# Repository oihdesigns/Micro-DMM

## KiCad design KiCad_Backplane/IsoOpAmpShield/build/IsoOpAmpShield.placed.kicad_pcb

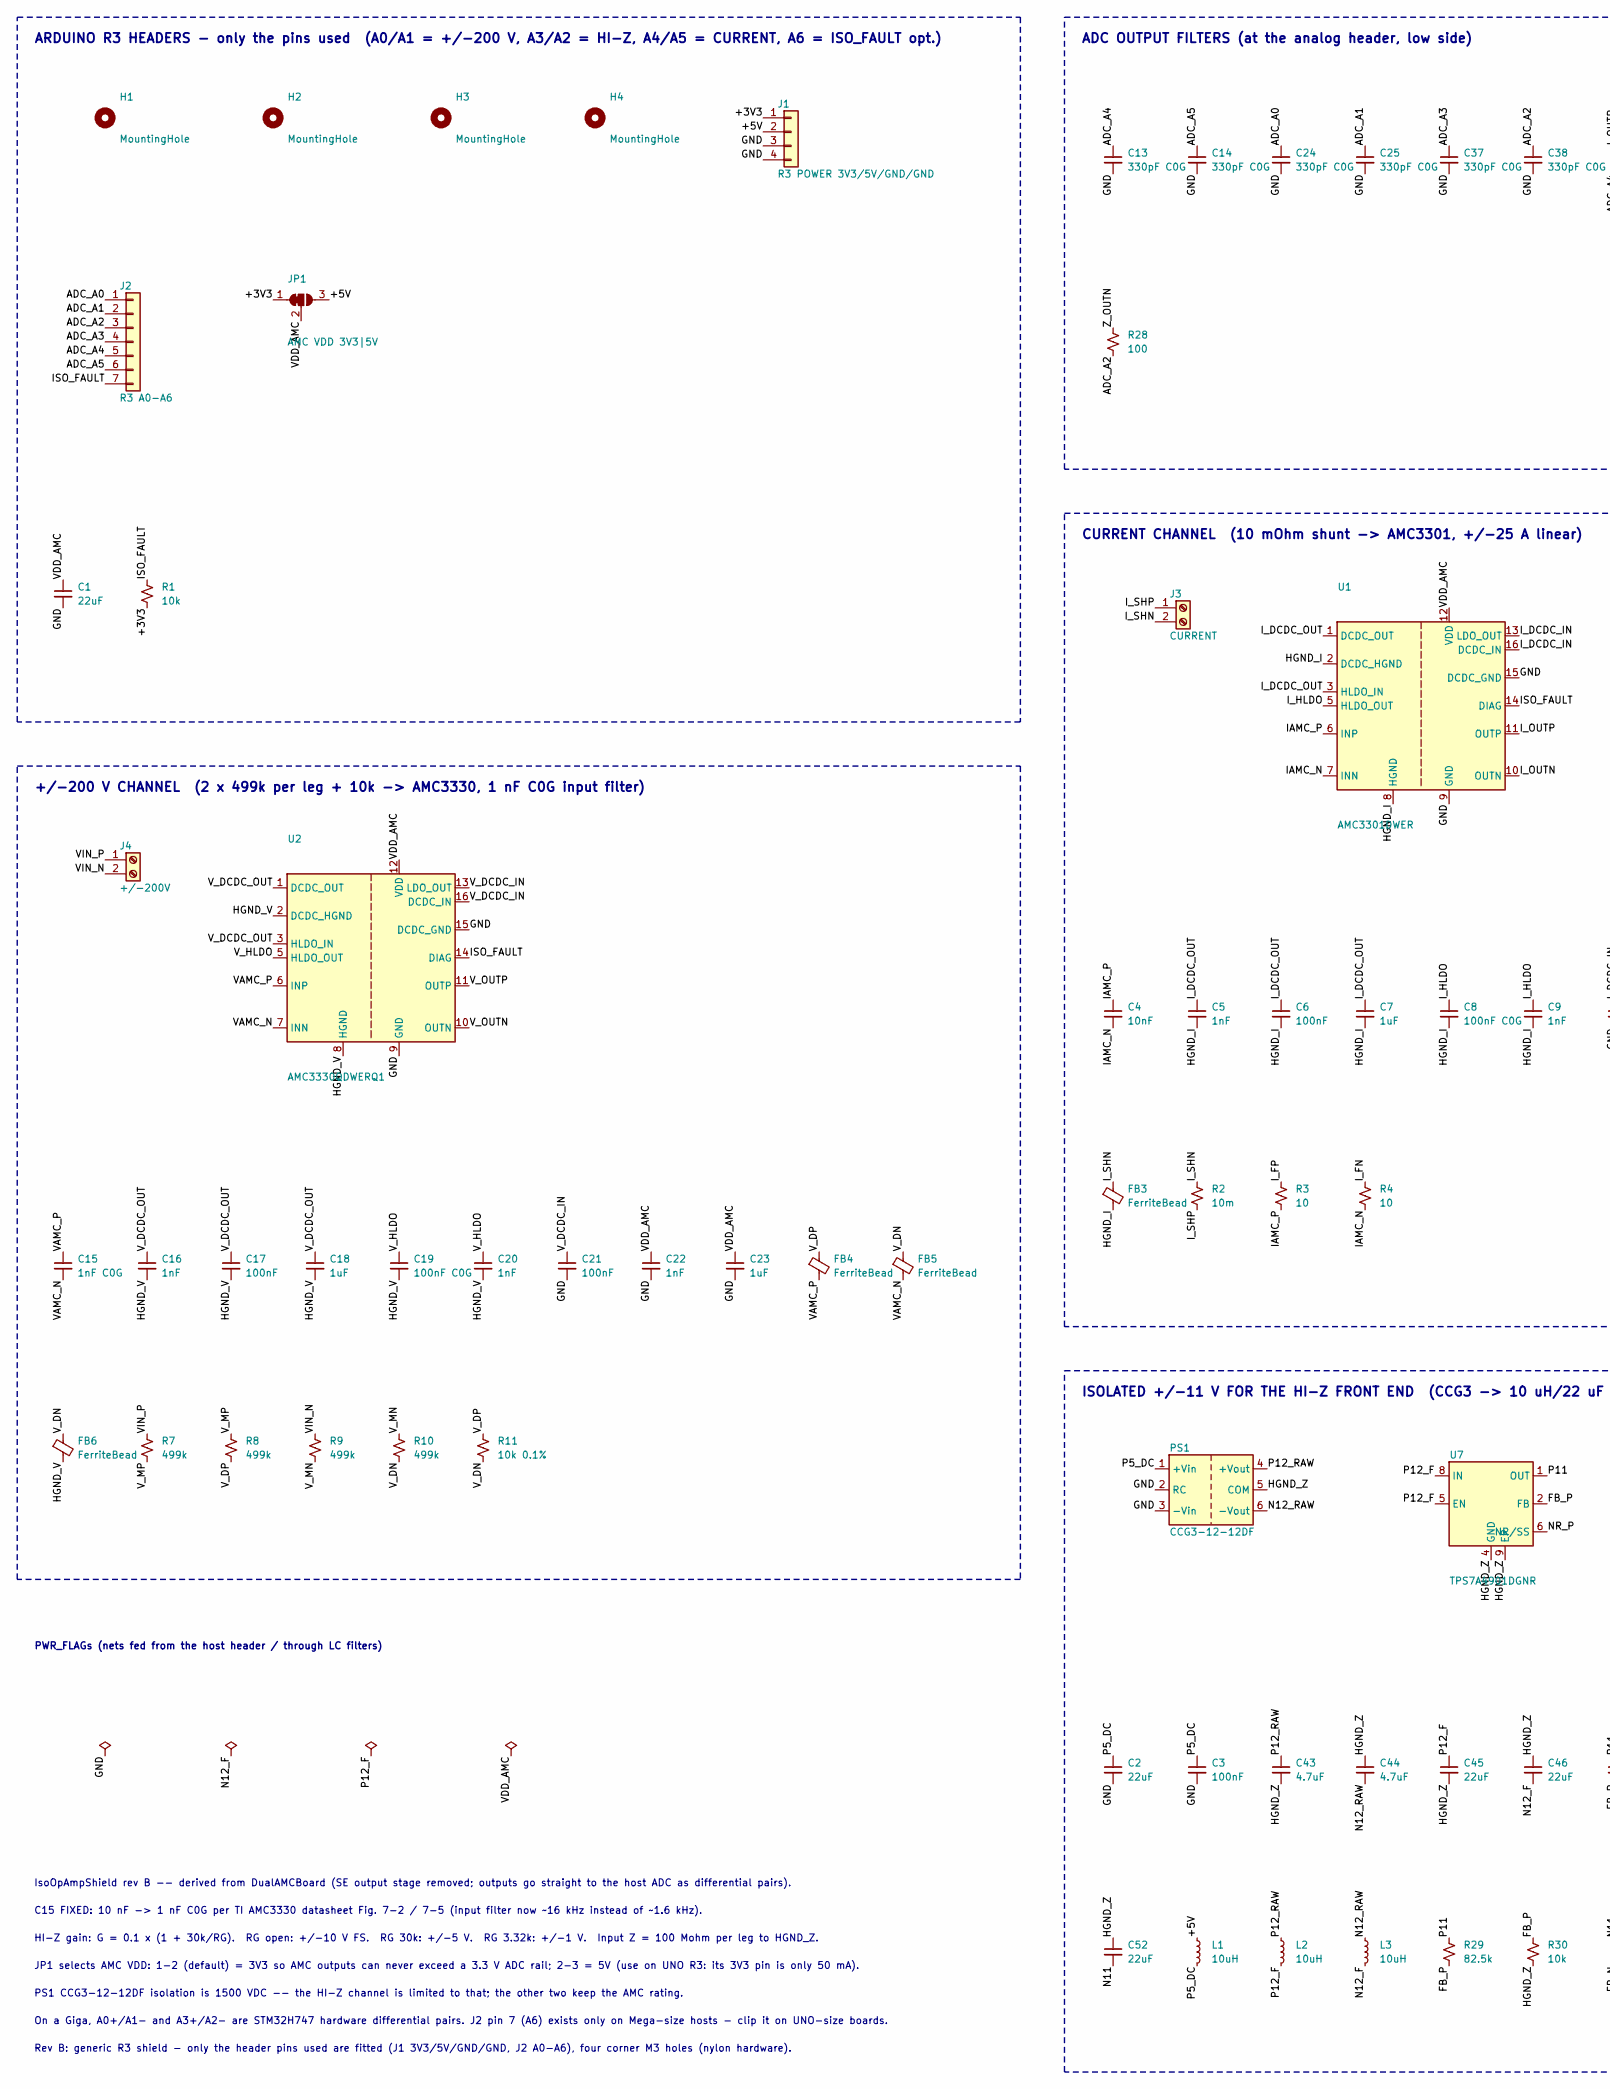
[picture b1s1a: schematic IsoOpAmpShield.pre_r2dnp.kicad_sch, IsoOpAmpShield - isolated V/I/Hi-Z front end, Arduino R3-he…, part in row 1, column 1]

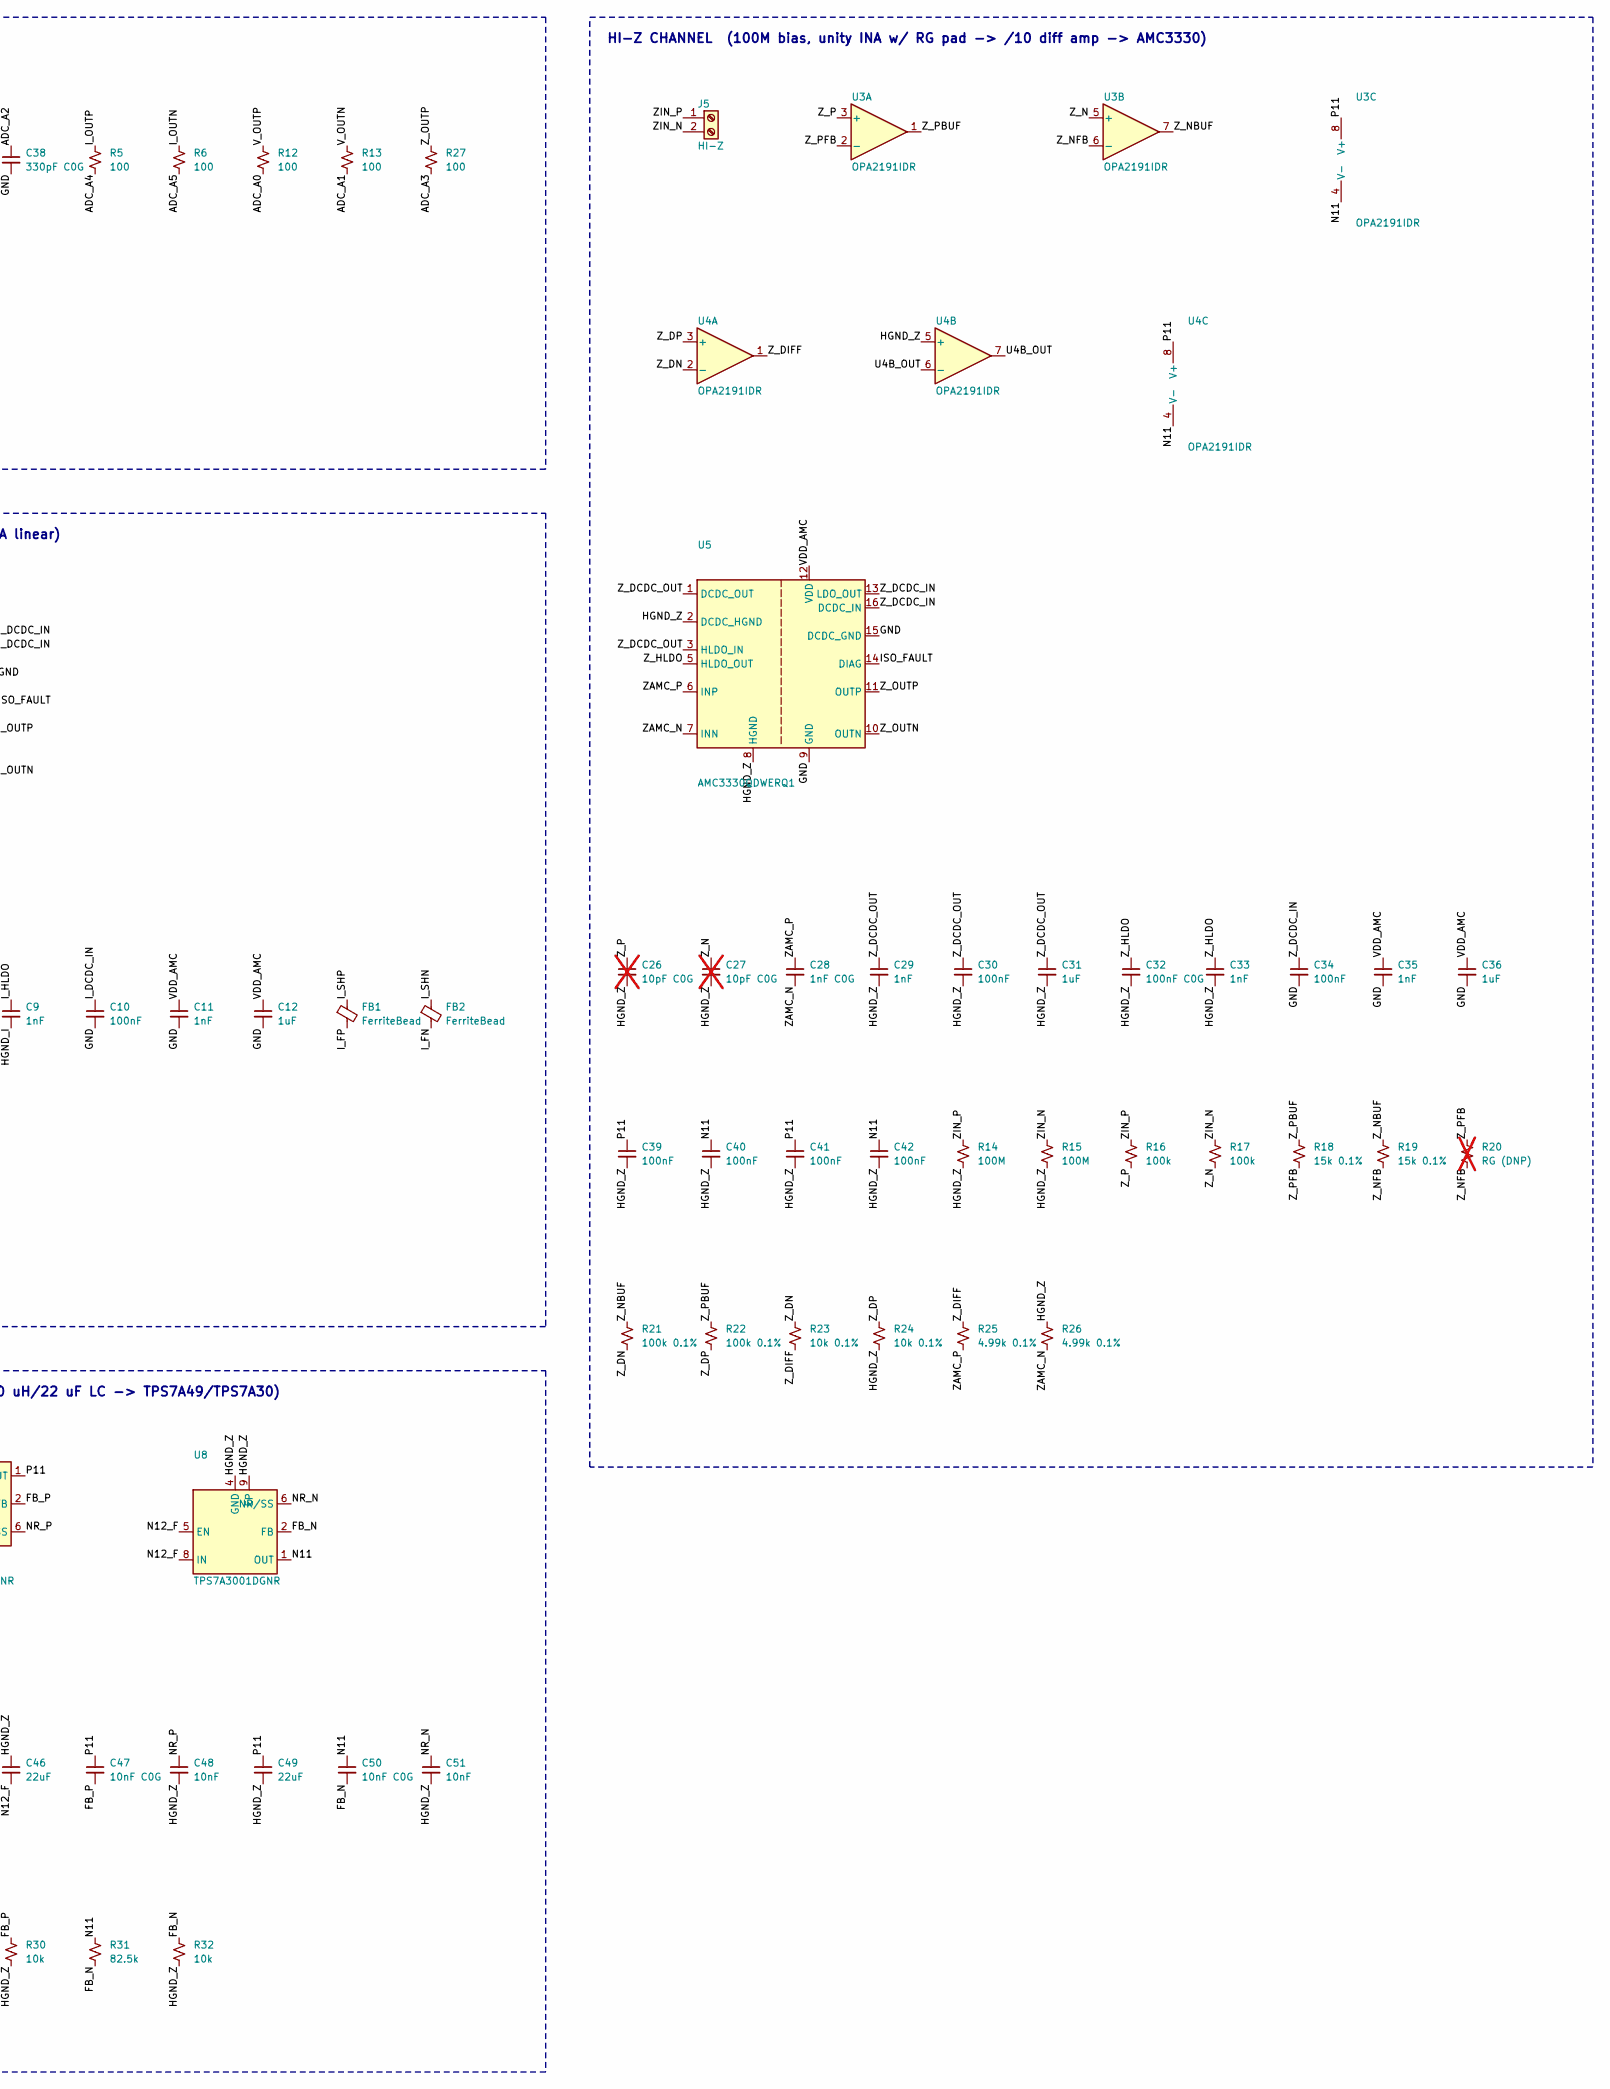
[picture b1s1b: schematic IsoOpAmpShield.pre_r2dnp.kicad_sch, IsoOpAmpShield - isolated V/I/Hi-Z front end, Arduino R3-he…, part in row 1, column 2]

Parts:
C1, C2, C45, C46, C49, C52: 22uF; C_0805_2012Metric_Pad1.18x1.45mm_HandSolder
C3, C6, C10, C17, C21, C30, C34, C39, C40, C41, C42: 100nF; C_0603_1608Metric_Pad1.08x0.95mm_HandSolder
C4: 10nF; C_0805_2012Metric_Pad1.18x1.45mm_HandSolder
C5, C16, C29: 1nF; C_0603_1608Metric_Pad1.08x0.95mm_HandSolder
C7, C18, C31: 1uF; C_0603_1608Metric_Pad1.08x0.95mm_HandSolder
C8, C19, C32: 100nF C0G; C_1206_3216Metric_Pad1.33x1.80mm_HandSolder
C9, C11, C20, C22, C33, C35: 1nF; C_1206_3216Metric_Pad1.33x1.80mm_HandSolder
C12, C23, C36: 1uF; C_1206_3216Metric_Pad1.33x1.80mm_HandSolder
C13, C14, C24, C25, C37, C38: 330pF C0G; C_0603_1608Metric_Pad1.08x0.95mm_HandSolder
C15, C28: 1nF C0G; C_0805_2012Metric_Pad1.18x1.45mm_HandSolder
C26, C27: 10pF C0G; C_0603_1608Metric_Pad1.08x0.95mm_HandSolder; not fitted
C43, C44: 4.7uF; C_0805_2012Metric_Pad1.18x1.45mm_HandSolder
C47, C50: 10nF C0G; C_0603_1608Metric_Pad1.08x0.95mm_HandSolder
C48, C51: 10nF; C_0603_1608Metric_Pad1.08x0.95mm_HandSolder
FB1, FB2, FB3, FB4, FB5, FB6: FerriteBead; L_0402_1005Metric_Pad0.77x0.64mm_HandSolder
H1, H2, H3, H4: MountingHole; MountingHole_3.2mm_M3_NPTH
J1: R3 POWER 3V3/5V/GND/GND; PinHeader_1x04_P2.54mm_Vertical
J2: R3 A0-A6; PinHeader_1x07_P2.54mm_Vertical
J3: CURRENT; TerminalBlock_RND_205-00232_1x02_P5.08mm_Horizontal
J4: +/-200V; TerminalBlock_RND_205-00232_1x02_P5.08mm_Horizontal
J5: HI-Z; TerminalBlock_RND_205-00232_1x02_P5.08mm_Horizontal
JP1: AMC VDD 3V3|5V; SolderJumper-3_P1.3mm_Bridged12_RoundedPad1.0x1.5mm
L1, L2, L3: 10uH; L_1210_3225Metric_Pad1.42x2.65mm_HandSolder
PS1: CCG3-12-12DF; TDK_CCG3_Dual_THT
R1, R30, R32: 10k; R_0805_2012Metric_Pad1.20x1.40mm_HandSolder
R2: 10m; R_2010_5025Metric_Pad1.40x2.65mm_HandSolder
R3, R4: 10; R_0805_2012Metric_Pad1.20x1.40mm_HandSolder
R5, R6, R12, R13, R27, R28: 100; R_0805_2012Metric_Pad1.20x1.40mm_HandSolder
R7, R8, R9, R10: 499k; R_0805_2012Metric_Pad1.20x1.40mm_HandSolder
R11, R23, R24: 10k 0.1%; R_0805_2012Metric_Pad1.20x1.40mm_HandSolder
R14, R15: 100M; R_1206_3216Metric_Pad1.30x1.75mm_HandSolder
R16, R17: 100k; R_1206_3216Metric_Pad1.30x1.75mm_HandSolder
R18, R19: 15k 0.1%; R_0805_2012Metric_Pad1.20x1.40mm_HandSolder
R20: RG (DNP); R_0805_2012Metric_Pad1.20x1.40mm_HandSolder; not fitted
R21, R22: 100k 0.1%; R_0805_2012Metric_Pad1.20x1.40mm_HandSolder
R25, R26: 4.99k 0.1%; R_0805_2012Metric_Pad1.20x1.40mm_HandSolder
R29, R31: 82.5k; R_0805_2012Metric_Pad1.20x1.40mm_HandSolder
U1: AMC3301DWER; SOIC-16W_7.5x10.3mm_P1.27mm
U2, U5: AMC3330QDWERQ1; SOIC-16W_7.5x10.3mm_P1.27mm
U3, U4: OPA2191IDR; SOIC-8_3.9x4.9mm_P1.27mm
U7: TPS7A4901DGNR; HVSSOP-8-1EP_3x3mm_P0.65mm_EP1.57x1.89mm
U8: TPS7A3001DGNR; HVSSOP-8-1EP_3x3mm_P0.65mm_EP1.57x1.89mm

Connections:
/+5V: J1.2, J1.5, JP1.3 (B), L1.1
/ADC_A0: C24.1, J2.1, R12.2
/ADC_A1: C25.1, J2.2, R13.2
/ADC_A2: C38.1, J2.3, R28.2
/ADC_A3: C37.1, J2.4, R27.2
/ADC_A4: C13.1, J2.5, R5.2
/ADC_A5: C14.1, J2.6, R6.2
/FB_N: C50.2, R31.2, R32.1, U8.2 (FB)
/FB_P: C47.2, R29.2, R30.1, U7.2 (FB)
/HGND_I: C5.2, C6.2, C7.2, C8.2, C9.2, FB3.2, U1.2 (DCDC_HGND), U1.8 (HGND)
/HGND_V: C16.2, C17.2, C18.2, C19.2, C20.2, FB6.2, U2.2 (DCDC_HGND), U2.8 (HGND)
/HGND_Z: C26.2, C27.2, C29.2, C30.2, C31.2, C32.2, C33.2, C39.2, C40.2, C41.2, C42.2, C43.2, C44.1, C45.2, C46.1, C48.2, C49.2, C51.2, C52.1, PS1.5 (COM), R14.2, R15.2, R24.2, R26.1, R30.2, R32.2, U4.5 (+), U5.2 (DCDC_HGND), U5.8 (HGND), U7.4 (GND), U7.9 (EP), U8.4 (GND), U8.9 (EP)
/IAMC_N: C4.2, R4.2, U1.7 (INN)
/IAMC_P: C4.1, R3.2, U1.6 (INP)
/ISO_FAULT: J2.7, R1.1, U1.14 (DIAG), U2.14 (DIAG), U5.14 (DIAG)
/I_DCDC_IN: C10.1, U1.13 (LDO_OUT), U1.16 (DCDC_IN)
/I_DCDC_OUT: C5.1, C6.1, C7.1, U1.1 (DCDC_OUT), U1.3 (HLDO_IN)
/I_FN: FB2.2, R4.1
/I_FP: FB1.2, R3.1
/I_HLDO: C8.1, C9.1, U1.5 (HLDO_OUT)
/I_OUTN: R6.1, U1.10 (OUTN)
/I_OUTP: R5.1, U1.11 (OUTP)
/I_SHN: FB2.1, FB3.1, J3.2, R2.1
/I_SHP: FB1.1, J3.1, R2.2
/N11: C40.1, C42.1, C50.1, C52.2, R31.1, U3.4 (V-), U4.4 (V-), U8.1 (OUT)
/N12_F: C46.2, L3.2, U8.5 (EN), U8.8 (IN)
/N12_RAW: C44.2, L3.1, PS1.6 (-Vout)
/NR_N: C51.1, U8.6 (NR/SS)
/NR_P: C48.1, U7.6 (NR/SS)
/P5_DC: C2.1, C3.1, L1.2, PS1.1 (+Vin)
/P11: C39.1, C41.1, C47.1, C49.1, R29.1, U3.8 (V+), U4.8 (V+), U7.1 (OUT)
/P12_F: C45.1, L2.2, U7.5 (EN), U7.8 (IN)
/P12_RAW: C43.1, L2.1, PS1.4 (+Vout)
/U4B_OUT: U4.6 (-), U4.7
/VAMC_N: C15.2, FB5.2, U2.7 (INN)
/VAMC_P: C15.1, FB4.2, U2.6 (INP)
/VDD_AMC: C1.1, C11.1, C12.1, C22.1, C23.1, C35.1, C36.1, JP1.2 (C), U1.12 (VDD), U2.12 (VDD), U5.12 (VDD)
/VIN_N: J4.2, R9.1
/VIN_P: J4.1, R7.1
/V_DCDC_IN: C21.1, U2.13 (LDO_OUT), U2.16 (DCDC_IN)
/V_DCDC_OUT: C16.1, C17.1, C18.1, U2.1 (DCDC_OUT), U2.3 (HLDO_IN)
/V_DN: FB5.1, FB6.1, R10.2, R11.2
/V_DP: FB4.1, R8.2, R11.1
/V_HLDO: C19.1, C20.1, U2.5 (HLDO_OUT)
/V_MN: R9.2, R10.1
/V_MP: R7.2, R8.1
/V_OUTN: R13.1, U2.10 (OUTN)
/V_OUTP: R12.1, U2.11 (OUTP)
/ZAMC_N: C28.2, R26.2, U5.7 (INN)
/ZAMC_P: C28.1, R25.2, U5.6 (INP)
/ZIN_N: J5.2, R15.1, R17.1
/ZIN_P: J5.1, R14.1, R16.1
/Z_DCDC_IN: C34.1, U5.13 (LDO_OUT), U5.16 (DCDC_IN)
/Z_DCDC_OUT: C29.1, C30.1, C31.1, U5.1 (DCDC_OUT), U5.3 (HLDO_IN)
/Z_DIFF: R23.2, R25.1, U4.1
/Z_DN: R21.2, R23.1, U4.2 (-)
/Z_DP: R22.2, R24.1, U4.3 (+)
/Z_HLDO: C32.1, C33.1, U5.5 (HLDO_OUT)
/Z_N: C27.1, R17.2, U3.5 (+)
/Z_NBUF: R19.1, R21.1, U3.7
/Z_NFB: R19.2, R20.2, U3.6 (-)
/Z_OUTN: R28.1, U5.10 (OUTN)
/Z_OUTP: R27.1, U5.11 (OUTP)
/Z_P: C26.1, R16.2, U3.3 (+)
/Z_PBUF: R18.1, R22.1, U3.1
/Z_PFB: R18.2, R20.1, U3.2 (-)

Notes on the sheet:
ARDUINO R3 HEADERS - only the pins used (A0/A1 = +/-200 V, A3/A2 = HI-Z, A4/A5 = CURRENT, A6 = ISO_FAULT opt.)
+/-200 V CHANNEL (2 x 499k per leg + 10k -> AMC3330, 1 nF C0G input filter)
ADC OUTPUT FILTERS (at the analog header, low side)
CURRENT CHANNEL (10 mOhm shunt -> AMC3301, +/-25 A linear)
ISOLATED +/-11 V FOR THE HI-Z FRONT END (CCG3 -> 10 uH/22 uF LC -> TPS7A49/TPS7A30)
HI-Z CHANNEL (100M bias, unity INA w/ RG pad -> /10 diff amp -> AMC3330)
PWR_FLAGs (nets fed from the host header / through LC filters)
IsoOpAmpShield rev B -- derived from DualAMCBoard (SE output stage removed; outputs go straight to the host ADC as differential pairs).
C15 FIXED: 10 nF -> 1 nF C0G per TI AMC3330 datasheet Fig. 7-2 / 7-5 (input filter now ~16 kHz instead of ~1.6 kHz).
HI-Z gain: G = 0.1 x (1 + 30k/RG). RG open: +/-10 V FS. RG 30k: +/-5 V. RG 3.32k: +/-1 V. Input Z = 100 Mohm per leg to HGND_Z.
JP1 selects AMC VDD: 1-2 (default) = 3V3 so AMC outputs can never exceed a 3.3 V ADC rail; 2-3 = 5V (use on UNO R3: its 3V3 pin is only 50 mA).
PS1 CCG3-12-12DF isolation is 1500 VDC -- the HI-Z channel is limited to that; the other two keep the AMC rating.
On a Giga, A0+/A1- and A3+/A2- are STM32H747 hardware differential pairs. J2 pin 7 (A6) exists only on Mega-size hosts - clip it on UNO-size boards.
Rev B: generic R3 shield - only the header pins used are fitted (J1 3V3/5V/GND/GND, J2 A0-A6), four corner M3 holes (nylon hardware).

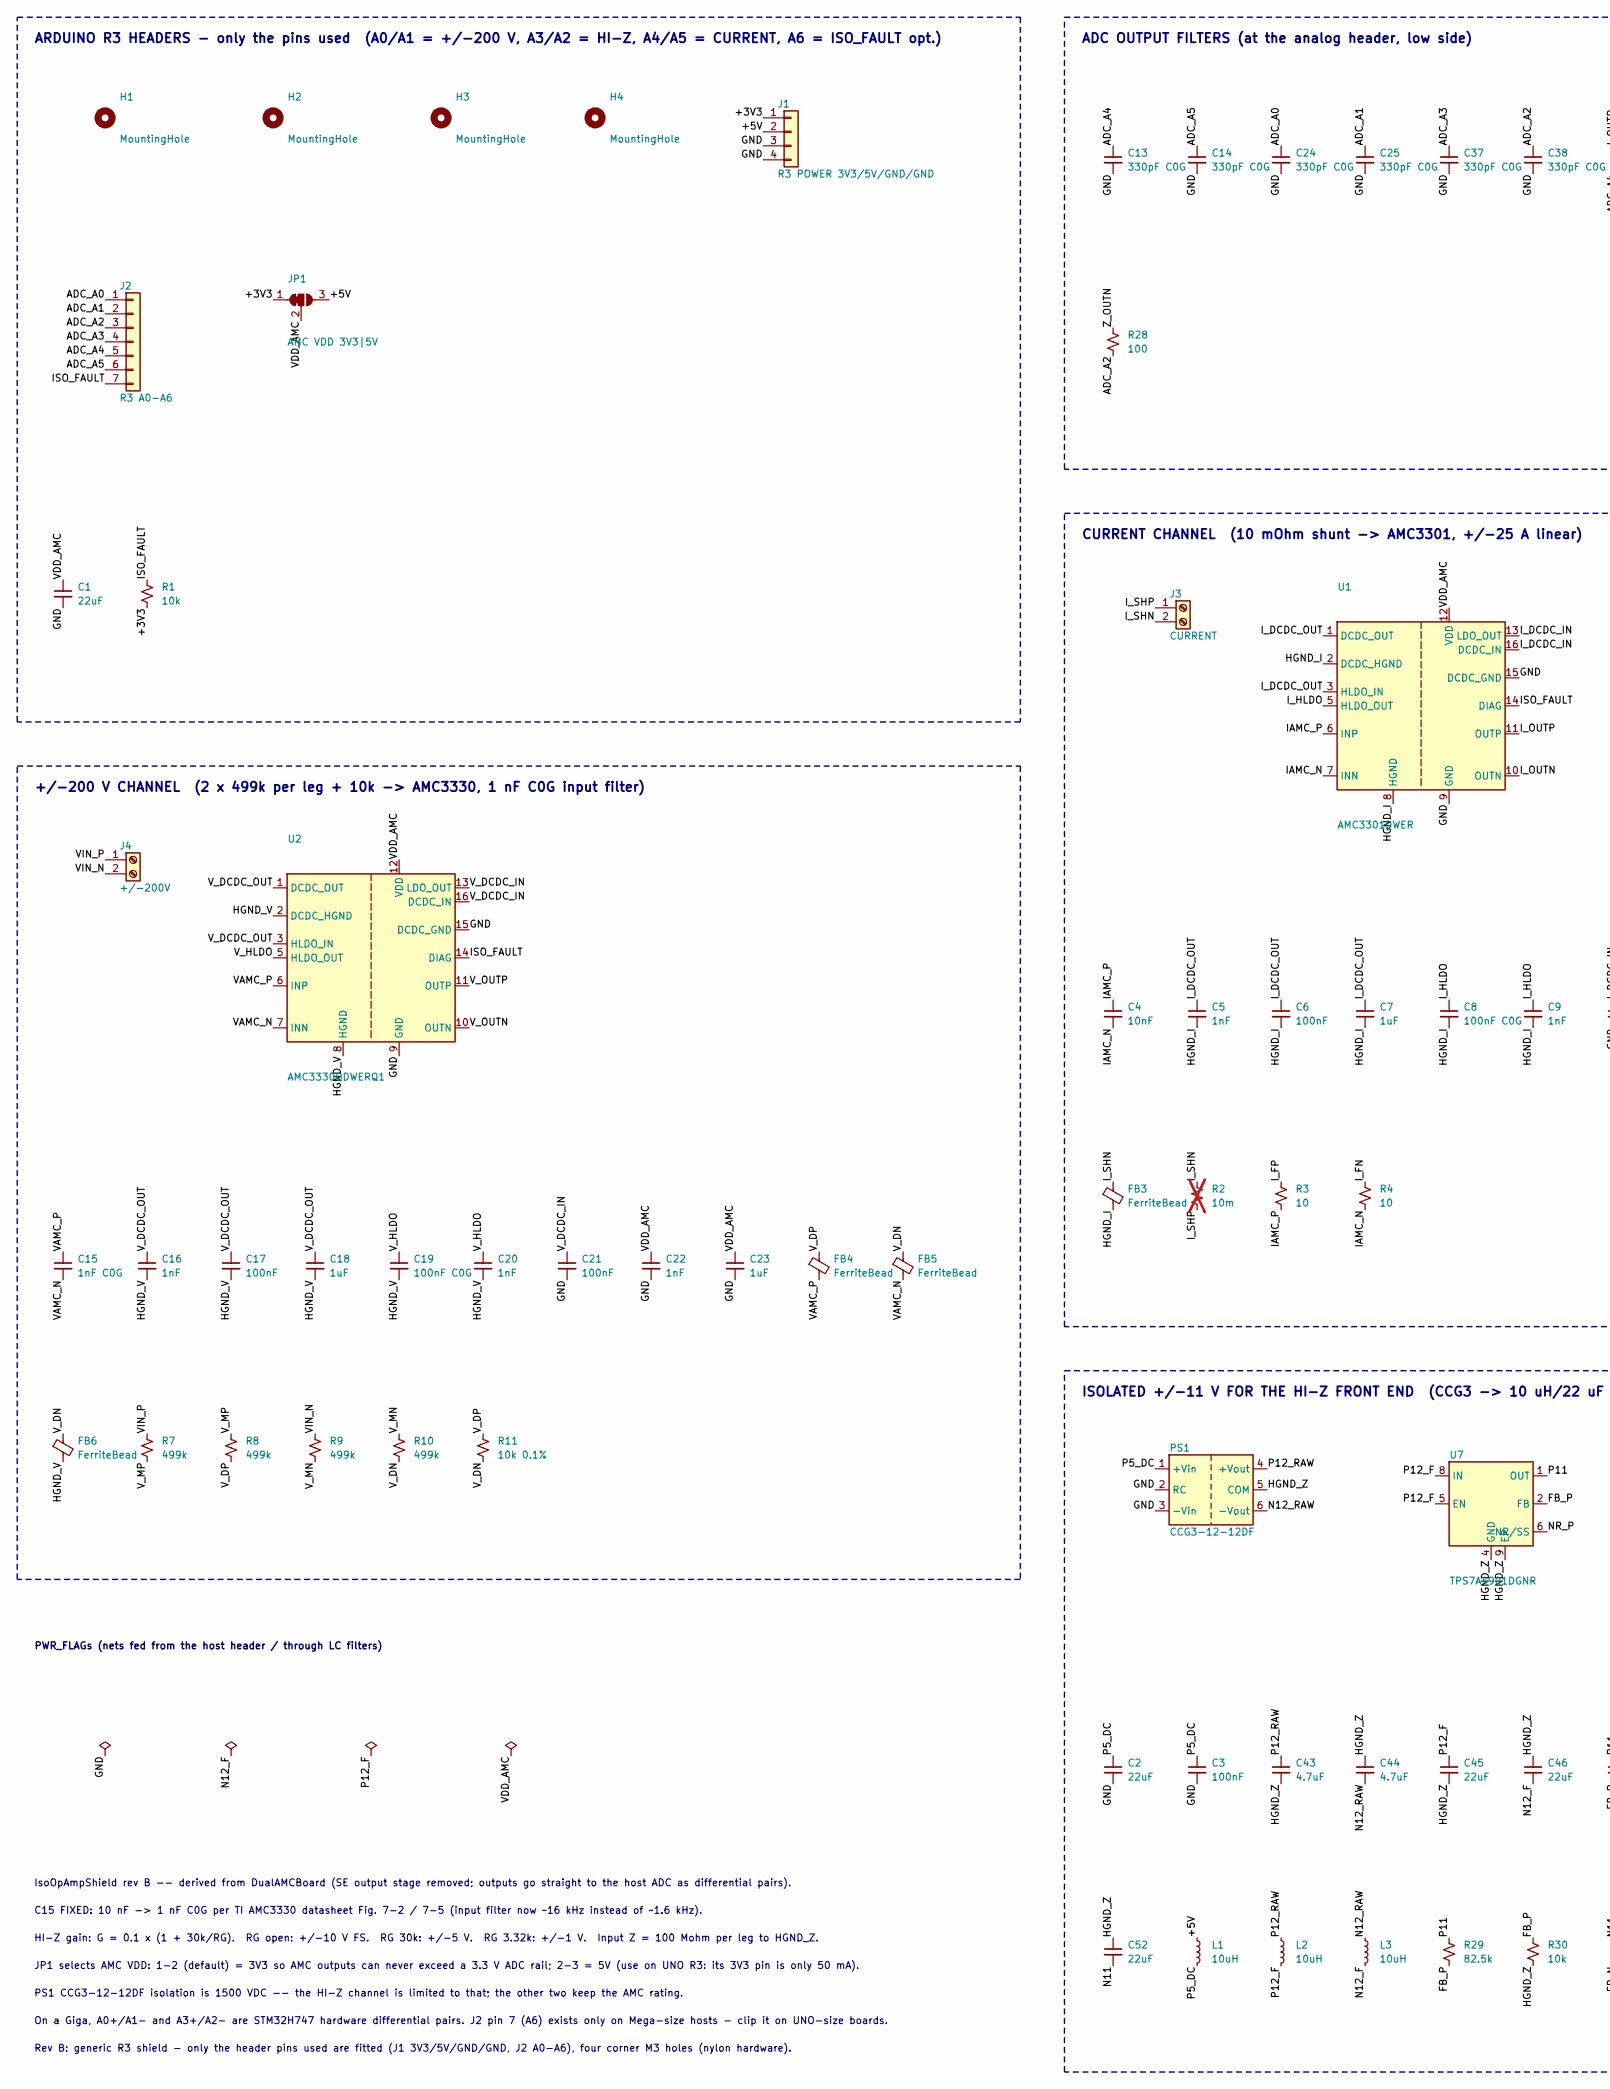
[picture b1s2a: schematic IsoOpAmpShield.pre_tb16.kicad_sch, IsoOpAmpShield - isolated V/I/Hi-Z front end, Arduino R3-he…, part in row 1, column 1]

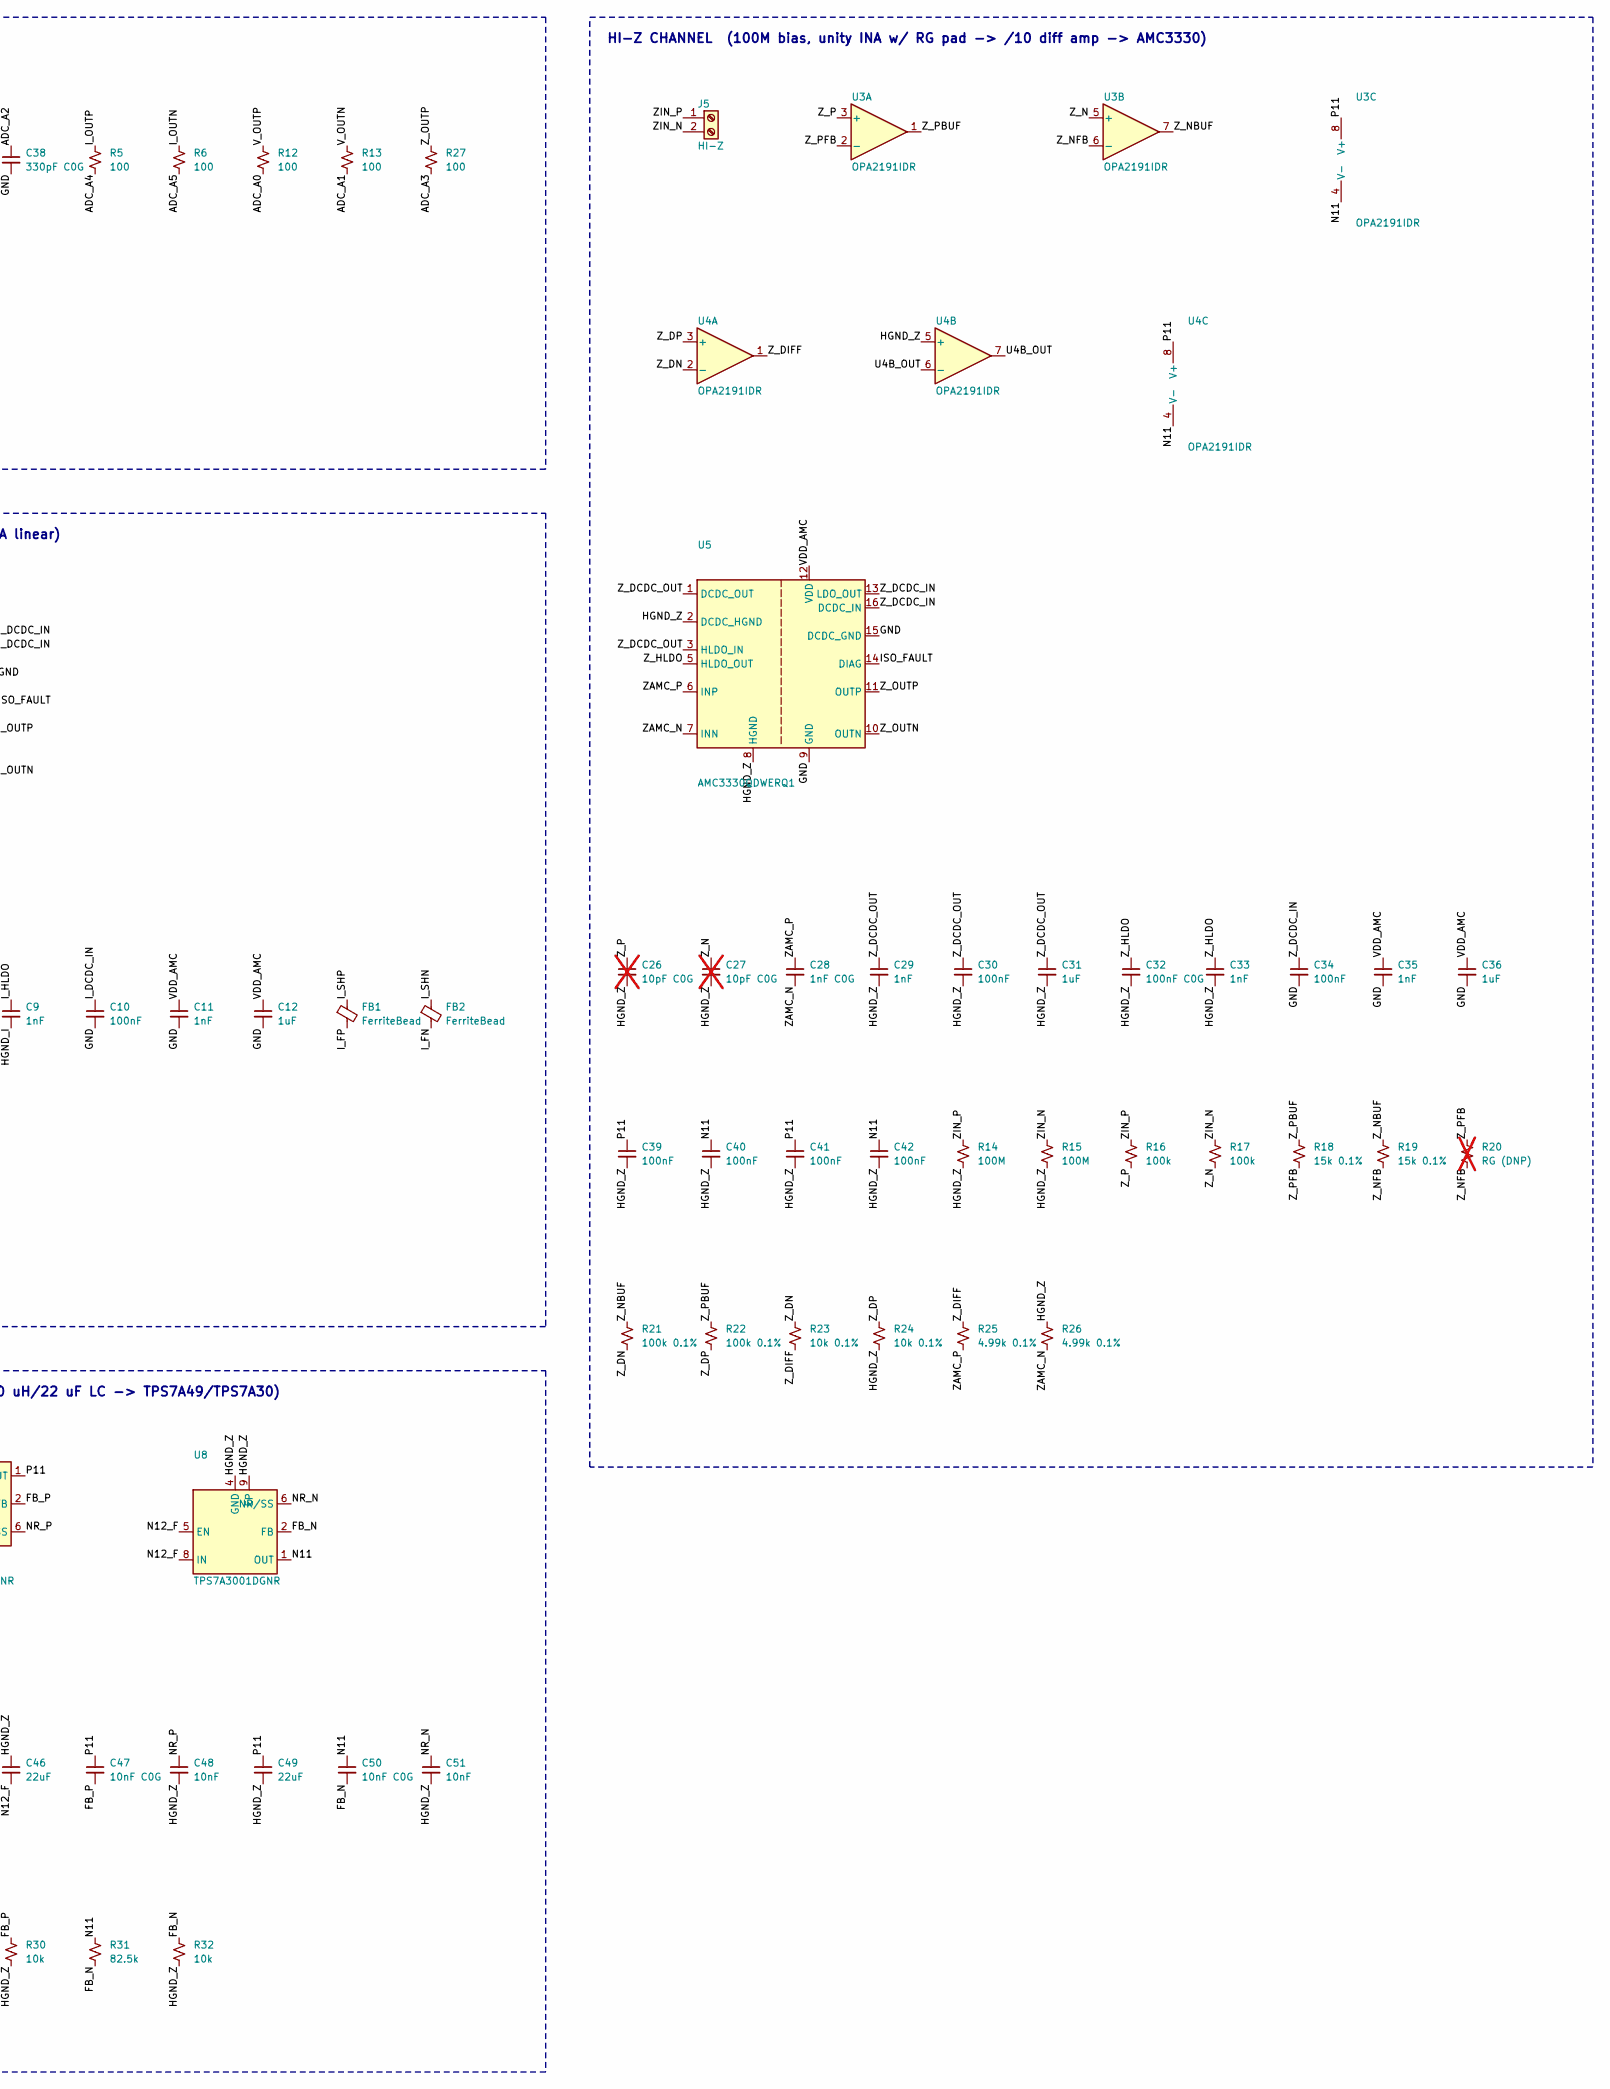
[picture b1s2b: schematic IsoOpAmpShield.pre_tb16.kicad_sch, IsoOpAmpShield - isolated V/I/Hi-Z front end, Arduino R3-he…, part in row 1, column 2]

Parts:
C1, C2, C45, C46, C49, C52: 22uF; C_0805_2012Metric_Pad1.18x1.45mm_HandSolder
C3, C6, C10, C17, C21, C30, C34, C39, C40, C41, C42: 100nF; C_0603_1608Metric_Pad1.08x0.95mm_HandSolder
C4: 10nF; C_0805_2012Metric_Pad1.18x1.45mm_HandSolder
C5, C16, C29: 1nF; C_0603_1608Metric_Pad1.08x0.95mm_HandSolder
C7, C18, C31: 1uF; C_0603_1608Metric_Pad1.08x0.95mm_HandSolder
C8, C19, C32: 100nF C0G; C_1206_3216Metric_Pad1.33x1.80mm_HandSolder
C9, C11, C20, C22, C33, C35: 1nF; C_1206_3216Metric_Pad1.33x1.80mm_HandSolder
C12, C23, C36: 1uF; C_1206_3216Metric_Pad1.33x1.80mm_HandSolder
C13, C14, C24, C25, C37, C38: 330pF C0G; C_0603_1608Metric_Pad1.08x0.95mm_HandSolder
C15, C28: 1nF C0G; C_0805_2012Metric_Pad1.18x1.45mm_HandSolder
C26, C27: 10pF C0G; C_0603_1608Metric_Pad1.08x0.95mm_HandSolder; not fitted
C43, C44: 4.7uF; C_0805_2012Metric_Pad1.18x1.45mm_HandSolder
C47, C50: 10nF C0G; C_0603_1608Metric_Pad1.08x0.95mm_HandSolder
C48, C51: 10nF; C_0603_1608Metric_Pad1.08x0.95mm_HandSolder
FB1, FB2, FB3, FB4, FB5, FB6: FerriteBead; L_0402_1005Metric_Pad0.77x0.64mm_HandSolder
H1, H2, H3, H4: MountingHole; MountingHole_3.2mm_M3_NPTH
J1: R3 POWER 3V3/5V/GND/GND; PinHeader_1x04_P2.54mm_Vertical
J2: R3 A0-A6; PinHeader_1x07_P2.54mm_Vertical
J3: CURRENT; TerminalBlock_RND_205-00232_1x02_P5.08mm_Horizontal
J4: +/-200V; TerminalBlock_RND_205-00232_1x02_P5.08mm_Horizontal
J5: HI-Z; TerminalBlock_RND_205-00232_1x02_P5.08mm_Horizontal
JP1: AMC VDD 3V3|5V; SolderJumper-3_P1.3mm_Bridged12_RoundedPad1.0x1.5mm
L1, L2, L3: 10uH; L_1210_3225Metric_Pad1.42x2.65mm_HandSolder
PS1: CCG3-12-12DF; TDK_CCG3_Dual_THT
R1, R30, R32: 10k; R_0805_2012Metric_Pad1.20x1.40mm_HandSolder
R2: 10m; R_2010_5025Metric_Pad1.40x2.65mm_HandSolder; not fitted
R3, R4: 10; R_0805_2012Metric_Pad1.20x1.40mm_HandSolder
R5, R6, R12, R13, R27, R28: 100; R_0805_2012Metric_Pad1.20x1.40mm_HandSolder
R7, R8, R9, R10: 499k; R_0805_2012Metric_Pad1.20x1.40mm_HandSolder
R11, R23, R24: 10k 0.1%; R_0805_2012Metric_Pad1.20x1.40mm_HandSolder
R14, R15: 100M; R_1206_3216Metric_Pad1.30x1.75mm_HandSolder
R16, R17: 100k; R_1206_3216Metric_Pad1.30x1.75mm_HandSolder
R18, R19: 15k 0.1%; R_0805_2012Metric_Pad1.20x1.40mm_HandSolder
R20: RG (DNP); R_0805_2012Metric_Pad1.20x1.40mm_HandSolder; not fitted
R21, R22: 100k 0.1%; R_0805_2012Metric_Pad1.20x1.40mm_HandSolder
R25, R26: 4.99k 0.1%; R_0805_2012Metric_Pad1.20x1.40mm_HandSolder
R29, R31: 82.5k; R_0805_2012Metric_Pad1.20x1.40mm_HandSolder
U1: AMC3301DWER; SOIC-16W_7.5x10.3mm_P1.27mm
U2, U5: AMC3330QDWERQ1; SOIC-16W_7.5x10.3mm_P1.27mm
U3, U4: OPA2191IDR; SOIC-8_3.9x4.9mm_P1.27mm
U7: TPS7A4901DGNR; HVSSOP-8-1EP_3x3mm_P0.65mm_EP1.57x1.89mm
U8: TPS7A3001DGNR; HVSSOP-8-1EP_3x3mm_P0.65mm_EP1.57x1.89mm

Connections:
/+5V: J1.2, J1.5, JP1.3 (B), L1.1
/ADC_A0: C24.1, J2.1, R12.2
/ADC_A1: C25.1, J2.2, R13.2
/ADC_A2: C38.1, J2.3, R28.2
/ADC_A3: C37.1, J2.4, R27.2
/ADC_A4: C13.1, J2.5, R5.2
/ADC_A5: C14.1, J2.6, R6.2
/FB_N: C50.2, R31.2, R32.1, U8.2 (FB)
/FB_P: C47.2, R29.2, R30.1, U7.2 (FB)
/HGND_I: C5.2, C6.2, C7.2, C8.2, C9.2, FB3.2, U1.2 (DCDC_HGND), U1.8 (HGND)
/HGND_V: C16.2, C17.2, C18.2, C19.2, C20.2, FB6.2, U2.2 (DCDC_HGND), U2.8 (HGND)
/HGND_Z: C26.2, C27.2, C29.2, C30.2, C31.2, C32.2, C33.2, C39.2, C40.2, C41.2, C42.2, C43.2, C44.1, C45.2, C46.1, C48.2, C49.2, C51.2, C52.1, PS1.5 (COM), R14.2, R15.2, R24.2, R26.1, R30.2, R32.2, U4.5 (+), U5.2 (DCDC_HGND), U5.8 (HGND), U7.4 (GND), U7.9 (EP), U8.4 (GND), U8.9 (EP)
/IAMC_N: C4.2, R4.2, U1.7 (INN)
/IAMC_P: C4.1, R3.2, U1.6 (INP)
/ISO_FAULT: J2.7, R1.1, U1.14 (DIAG), U2.14 (DIAG), U5.14 (DIAG)
/I_DCDC_IN: C10.1, U1.13 (LDO_OUT), U1.16 (DCDC_IN)
/I_DCDC_OUT: C5.1, C6.1, C7.1, U1.1 (DCDC_OUT), U1.3 (HLDO_IN)
/I_FN: FB2.2, R4.1
/I_FP: FB1.2, R3.1
/I_HLDO: C8.1, C9.1, U1.5 (HLDO_OUT)
/I_OUTN: R6.1, U1.10 (OUTN)
/I_OUTP: R5.1, U1.11 (OUTP)
/I_SHN: FB2.1, FB3.1, J3.2, R2.1
/I_SHP: FB1.1, J3.1, R2.2
/N11: C40.1, C42.1, C50.1, C52.2, R31.1, U3.4 (V-), U4.4 (V-), U8.1 (OUT)
/N12_F: C46.2, L3.2, U8.5 (EN), U8.8 (IN)
/N12_RAW: C44.2, L3.1, PS1.6 (-Vout)
/NR_N: C51.1, U8.6 (NR/SS)
/NR_P: C48.1, U7.6 (NR/SS)
/P5_DC: C2.1, C3.1, L1.2, PS1.1 (+Vin)
/P11: C39.1, C41.1, C47.1, C49.1, R29.1, U3.8 (V+), U4.8 (V+), U7.1 (OUT)
/P12_F: C45.1, L2.2, U7.5 (EN), U7.8 (IN)
/P12_RAW: C43.1, L2.1, PS1.4 (+Vout)
/U4B_OUT: U4.6 (-), U4.7
/VAMC_N: C15.2, FB5.2, U2.7 (INN)
/VAMC_P: C15.1, FB4.2, U2.6 (INP)
/VDD_AMC: C1.1, C11.1, C12.1, C22.1, C23.1, C35.1, C36.1, JP1.2 (C), U1.12 (VDD), U2.12 (VDD), U5.12 (VDD)
/VIN_N: J4.2, R9.1
/VIN_P: J4.1, R7.1
/V_DCDC_IN: C21.1, U2.13 (LDO_OUT), U2.16 (DCDC_IN)
/V_DCDC_OUT: C16.1, C17.1, C18.1, U2.1 (DCDC_OUT), U2.3 (HLDO_IN)
/V_DN: FB5.1, FB6.1, R10.2, R11.2
/V_DP: FB4.1, R8.2, R11.1
/V_HLDO: C19.1, C20.1, U2.5 (HLDO_OUT)
/V_MN: R9.2, R10.1
/V_MP: R7.2, R8.1
/V_OUTN: R13.1, U2.10 (OUTN)
/V_OUTP: R12.1, U2.11 (OUTP)
/ZAMC_N: C28.2, R26.2, U5.7 (INN)
/ZAMC_P: C28.1, R25.2, U5.6 (INP)
/ZIN_N: J5.2, R15.1, R17.1
/ZIN_P: J5.1, R14.1, R16.1
/Z_DCDC_IN: C34.1, U5.13 (LDO_OUT), U5.16 (DCDC_IN)
/Z_DCDC_OUT: C29.1, C30.1, C31.1, U5.1 (DCDC_OUT), U5.3 (HLDO_IN)
/Z_DIFF: R23.2, R25.1, U4.1
/Z_DN: R21.2, R23.1, U4.2 (-)
/Z_DP: R22.2, R24.1, U4.3 (+)
/Z_HLDO: C32.1, C33.1, U5.5 (HLDO_OUT)
/Z_N: C27.1, R17.2, U3.5 (+)
/Z_NBUF: R19.1, R21.1, U3.7
/Z_NFB: R19.2, R20.2, U3.6 (-)
/Z_OUTN: R28.1, U5.10 (OUTN)
/Z_OUTP: R27.1, U5.11 (OUTP)
/Z_P: C26.1, R16.2, U3.3 (+)
/Z_PBUF: R18.1, R22.1, U3.1
/Z_PFB: R18.2, R20.1, U3.2 (-)

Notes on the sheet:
ARDUINO R3 HEADERS - only the pins used (A0/A1 = +/-200 V, A3/A2 = HI-Z, A4/A5 = CURRENT, A6 = ISO_FAULT opt.)
+/-200 V CHANNEL (2 x 499k per leg + 10k -> AMC3330, 1 nF C0G input filter)
ADC OUTPUT FILTERS (at the analog header, low side)
CURRENT CHANNEL (10 mOhm shunt -> AMC3301, +/-25 A linear)
ISOLATED +/-11 V FOR THE HI-Z FRONT END (CCG3 -> 10 uH/22 uF LC -> TPS7A49/TPS7A30)
HI-Z CHANNEL (100M bias, unity INA w/ RG pad -> /10 diff amp -> AMC3330)
PWR_FLAGs (nets fed from the host header / through LC filters)
IsoOpAmpShield rev B -- derived from DualAMCBoard (SE output stage removed; outputs go straight to the host ADC as differential pairs).
C15 FIXED: 10 nF -> 1 nF C0G per TI AMC3330 datasheet Fig. 7-2 / 7-5 (input filter now ~16 kHz instead of ~1.6 kHz).
HI-Z gain: G = 0.1 x (1 + 30k/RG). RG open: +/-10 V FS. RG 30k: +/-5 V. RG 3.32k: +/-1 V. Input Z = 100 Mohm per leg to HGND_Z.
JP1 selects AMC VDD: 1-2 (default) = 3V3 so AMC outputs can never exceed a 3.3 V ADC rail; 2-3 = 5V (use on UNO R3: its 3V3 pin is only 50 mA).
PS1 CCG3-12-12DF isolation is 1500 VDC -- the HI-Z channel is limited to that; the other two keep the AMC rating.
On a Giga, A0+/A1- and A3+/A2- are STM32H747 hardware differential pairs. J2 pin 7 (A6) exists only on Mega-size hosts - clip it on UNO-size boards.
Rev B: generic R3 shield - only the header pins used are fitted (J1 3V3/5V/GND/GND, J2 A0-A6), four corner M3 holes (nylon hardware).

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
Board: 4 copper layers, 110 parts (0 on the bottom side), 68 nets, no tracks yet.
